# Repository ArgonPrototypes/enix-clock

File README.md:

# Enix: The Modern Nixie Clock
### A beautifully sleek product that gives new life to vintage components
#### Learn more at our website: https://www.argonprototypes.com/
This repository contains hardware, software, CAD files, and much more!

# More info about each section:
## Electronic Hardware:
The circuit board was designed in EAGLE CAD V9.2.2. Most dimensions are in mm on this board. The Gerber files are in RS-274X and Excellon drill format. There are several external libraries used; Sparkfun, Adafruit, MacroFab, and a couple more for unique parts. There should not be any problems with opening the design files without the libraries installed.

## Software:
The majority of the software is written in VS Code with the PlatformIO extension, however the Arduino IDE works just as well. The microcontroller used is the ATMega32u4, which has an 8 bit architecture with a 16MHz clock speed, is 5V tolerant, and includes built in USB programmability. This microcontroller is found on the Arduino Micro, which can be selected from the IDE to be able to upload to the board.<br/> The libraries used are Arduino.h, TimerOne.h, RTClib.h, Adafruit_NeoPixel.h, Adafruit MCP9808.h, Wire.h, and EEPROM.h.

## Case
The outer case is a CNC milled block of Aluminum or Wood. The Aluminum cases are Vapour Blasted to give a satin look, and then Anodized in Black or Clear to add a protective coating. The Wood cases are sanded to a smooth finish, prior to coating in polyurethane or oil. <br/> To hold the electronics in the case, there is a 3D printed bottom plate which uses heat set inserts to bolt to the circuit board.

## Packaging
To safely ship the Enix, a custom cardboard box with the internal dimensions of 6x6x3" was designed and ordered through Packlane. 2 Foam CNC milled inserts tightly pack the clock and all included accessories, which includes the Enix, some stickers, a drink coaster, instruction manual, and a Mini-USB cable.<br/>
The Packlane box is shipped in a larger 8x8x5" standard cardboard box filled with packing peanuts to give added protection in shipping.

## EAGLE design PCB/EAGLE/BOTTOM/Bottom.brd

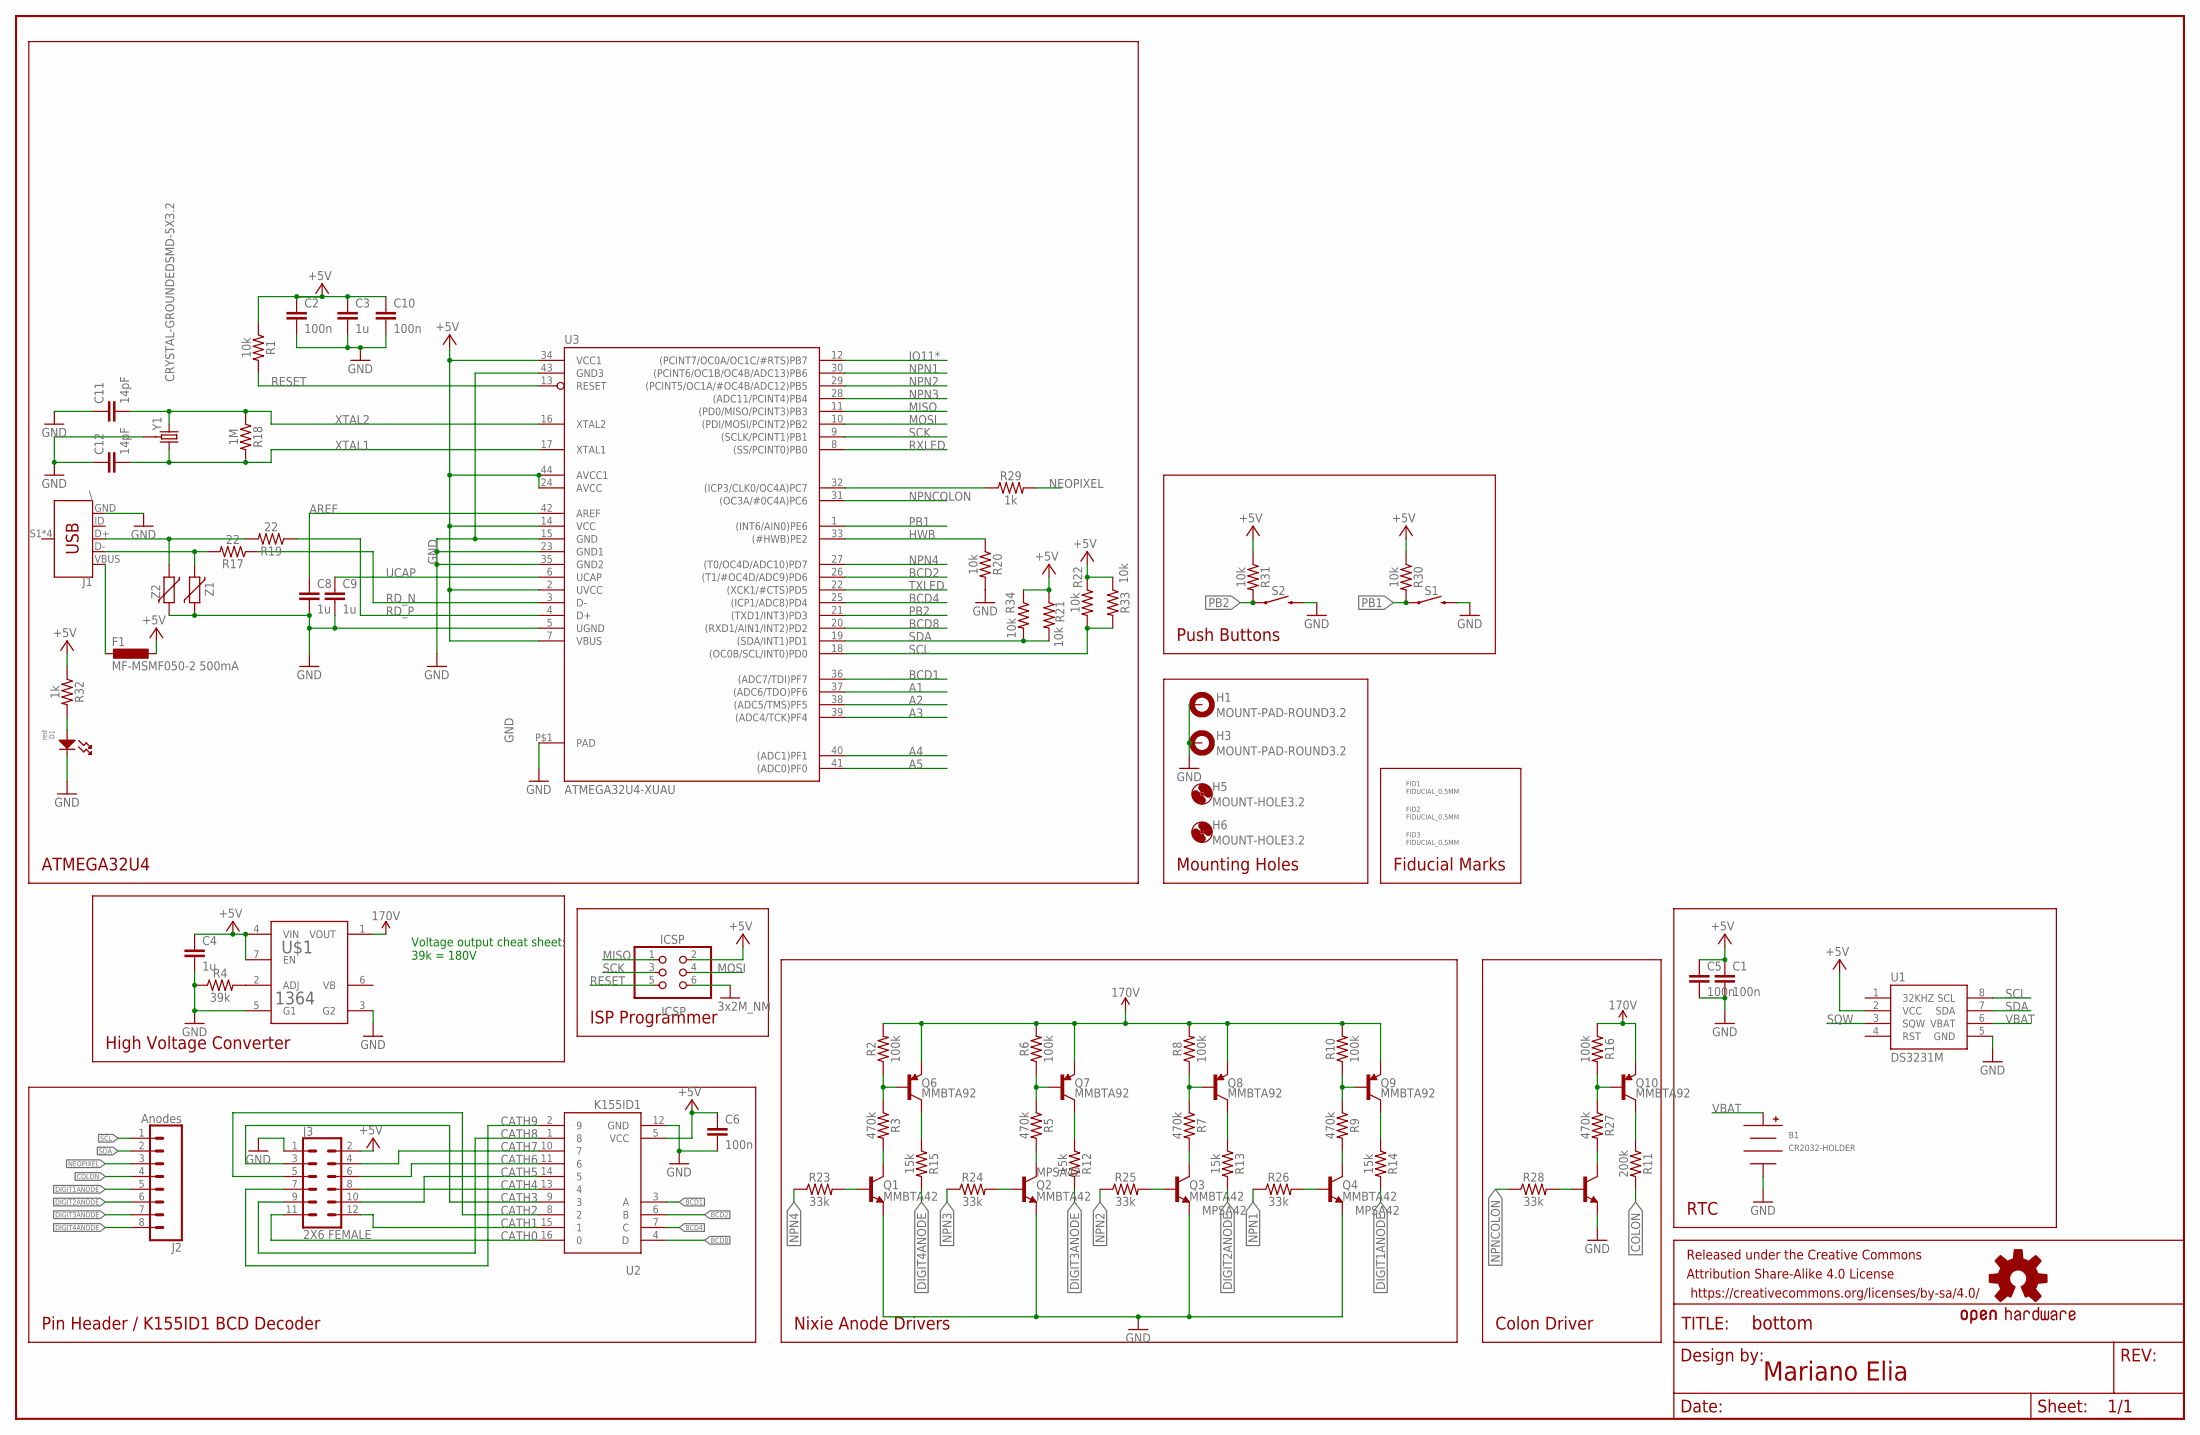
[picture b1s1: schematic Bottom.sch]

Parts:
B1: CR2032-HOLDER; CH28-2032LF
C1, C2, C5, C6, C10: 100n; 0805
C3, C4, C8, C9: 1u; 0805
C11, C12: 14pF; 0805
D1: red; LED0805
F1: MF-MSMF050-2 500mA; L1812
FID1, FID2, FID3: FIDUCIAL_0.5MM
FRAME1: FRAME-LEDGER; CREATIVE_COMMONS
H1, H3: MOUNT-PAD-ROUND3.2; 3,2-PAD
H5, H6: MOUNT-HOLE3.2; 3,2
ICSP: ICSP; 2X03
J1: \; USB-MINIB
J2: Anodes; 1X08_NO_SILK
J3: 2X6 FEMALE; 2X6_NOSILK
LOGO1: OSHW-LOGOL; OSHW-LOGO-L
Q1, Q2, Q3, Q4, Q5: MMBTA42; SOT23-3
Q6, Q7, Q8, Q9, Q10: MMBTA92; SOT23-3
R1, R20, R21, R22, R30, R31, R33, R34: 10k; 0805
R2, R6, R8, R10, R16: 100k; 0805
R3, R5, R7, R9, R27: 470k; 0805
R4: 39k; 0805
R11: 200k; 0805
R12, R13, R14, R15: 15k; 0805
R17, R19: 22; 0805
R18: 1M; 0805
R23, R24, R25, R26, R28: 33k; 0805
R29, R32: 1k; 0805
S1, S2: MOMENTARY-SWITCH-SPST-PTH-RIGHT-ANGLE-KIT; TACTILE_SWITCH_PTH_RIGHT_ANGLE_KIT
U1: DS3231M; SO08
U2: K155ID1; DIL16-KIT
U3: ATMEGA32U4-XUAU; TQFP44-PAD
U$1: 1364
Y1: CRYSTAL-GROUNDEDSMD-5X3.2; CRYSTAL-SMD-5X3.2-4PAD
Z1, Z2: VARISTORCN0603; CT/CN0603

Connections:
170V: Q6.2 (E), Q7.2 (E), Q8.2 (E), Q9.2 (E), Q10.2 (E), R2.2, R6.2, R8.2, R10.2, R16.1, U$1.1 (VOUT)
+5V: C1.1, C2.1, C3.1, C4.1, C5.1, C6.1, C10.1, F1.1, ICSP.2, J3.2, R1.1, R21.1, R22.1, R30.1, R31.1, R32.1, R33.1, R34.1, U1.2 (VCC), U2.5 (VCC), U3.2 (UVCC), U3.7 (VBUS), U3.14 (VCC), U3.24 (AVCC), U3.34 (VCC1), U3.44 (AVCC1), U$1.4 (VIN), U$1.7 (EN)
A1: U3.37 ((ADC6/TDO)PF6)
A2: U3.38 ((ADC5/TMS)PF5)
A3: U3.39 ((ADC4/TCK)PF4)
A4: U3.40 ((ADC1)PF1)
A5: U3.41 ((ADC0)PF0)
AREF: C8.1, U3.42 (AREF)
BCD1: U2.3 (A), U3.36 ((ADC7/TDI)PF7)
BCD2: U2.6 (B), U3.26 ((T1/#OC4D/ADC9)PD6)
BCD4: U2.7 (C), U3.25 ((ICP1/ADC8)PD4)
BCD8: U2.4 (D), U3.20 ((RXD1/AIN1/INT2)PD2)
CATH0: J3.11, U2.16 (0)
CATH1: J3.12, U2.15 (1)
CATH2: J3.5, U2.8 (2)
CATH3: J3.3, U2.9 (3)
CATH4: J3.8, U2.13 (4)
CATH5: J3.10, U2.14 (5)
CATH6: J3.6, U2.11 (6)
CATH7: J3.4, U2.10 (7)
CATH8: J3.9, U2.1 (8)
CATH9: J3.7, U2.2 (9)
COLON: J2.4, R11.2
DIGIT1ANODE: J2.5, R14.2
DIGIT2ANODE: J2.6, R13.2
DIGIT3ANODE: J2.7, R12.2
DIGIT4ANODE: J2.8, R15.2
D_N: J1.D-, R17.2, Z1.1
D_P: J1.D+, R19.2, Z2.1
GND: B1.NEG, C1.2, C2.2, C3.2, C4.2, C5.2, C6.2, C8.2, C9.2, C10.2, C11.1, C12.1, D1.CATHODE, H1.B3,2, H3.B3,2, ICSP.6, J1.GND, J3.1, Q1.2 (E), Q2.2 (E), Q3.2 (E), Q4.2 (E), Q5.2 (E), R4.1, R20.2, S1.2, S2.2, U1.5 (GND), U2.12 (GND), U3.5 (UGND), U3.15 (GND), U3.23 (GND1), U3.35 (GND2), U3.43 (GND3), U3.P$1 (PAD), U$1.3 (G2), U$1.5 (G1), Y1.2 (3), Y1.4 (3), Z1.2, Z2.2
HWB: R20.1, U3.33 ((#HWB)PE2)
IO11*: U3.12 ((PCINT7/OC0A/OC1C/#RTS)PB7)
MISO: ICSP.1, U3.11 ((PD0/MISO/PCINT3)PB3)
MOSI: ICSP.4, U3.10 ((PDI/MOSI/PCINT2)PB2)
unnamed: Q1.1 (B), R23.2
unnamed: Q2.1 (B), R24.2
unnamed: R4.2, U$1.2 (ADJ)
unnamed: Q3.1 (B), R25.2
unnamed: Q4.1 (B), R26.2
unnamed: Q6.1 (B), R2.1, R3.1
unnamed: Q1.3 (C), R3.2
unnamed: Q7.1 (B), R5.1, R6.1
unnamed: Q8.1 (B), R7.1, R8.1
unnamed: Q9.1 (B), R9.1, R10.1
unnamed: Q4.3 (C), R9.2
unnamed: Q2.3 (C), R5.2
unnamed: Q3.3 (C), R7.2
unnamed: Q5.1 (B), R28.2
unnamed: Q10.1 (B), R16.2, R27.1
unnamed: R29.1, U3.32 ((ICP3/CLK0/OC4A)PC7)
unnamed: Q5.3 (C), R27.2
unnamed: D1.ANODE, R32.2
unnamed: Q10.3 (C), R11.1
unnamed: Q7.3 (C), R12.1
unnamed: Q6.3 (C), R15.1
unnamed: Q8.3 (C), R13.1
unnamed: Q9.3 (C), R14.1
NEOPIXEL: J2.3, R29.2
NPN1: R26.1, U3.30 ((PCINT6/OC1B/OC4B/ADC13)PB6)
NPN2: R25.1, U3.29 ((PCINT5/OC1A/#OC4B/ADC12)PB5)
NPN3: R24.1, U3.28 ((ADC11/PCINT4)PB4)
NPN4: R23.1, U3.27 ((T0/OC4D/ADC10)PD7)
NPNCOLON: R28.1, U3.31 ((OC3A/#0C4A)PC6)
PB1: R30.2, S1.1, U3.1 ((INT6/AIN0)PE6)
PB2: R31.2, S2.1, U3.21 ((TXD1/INT3)PD3)
RD_N: R17.1, U3.3 (D-)
RD_P: R19.1, U3.4 (D+)
RESET: ICSP.5, R1.2, U3.13 (RESET)
RXLED: U3.8 ((SS/PCINT0)PB0)
SCK: ICSP.3, U3.9 ((SCLK/PCINT1)PB1)
SCL: J2.1, R22.2, R33.2, U1.8 (SCL), U3.18 ((OC0B/SCL/INT0)PD0)
SDA: J2.2, R21.2, R34.2, U1.7 (SDA), U3.19 ((SDA/INT1)PD1)
SQW: U1.3 (SQW)
TXLED: U3.22 ((XCK1/#CTS)PD5)
UCAP: C9.1, U3.6 (UCAP)
VBAT: B1.POS, U1.6 (VBAT)
VBUS: F1.2, J1.VBUS
XTAL1: C12.2, R18.2, U3.17 (XTAL1), Y1.1 (2)
XTAL2: C11.2, R18.1, U3.16 (XTAL2), Y1.3 (1)

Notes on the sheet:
ATMEGA32U4
High Voltage Converter
Pin Header / K155ID1 BCD Decoder
Nixie Anode Drivers
Colon Driver
RTC
Mariano Elia
Push Buttons
Mounting Holes
Fiducial Marks
ISP Programmer
Voltage output cheat sheet: 39k = 180V

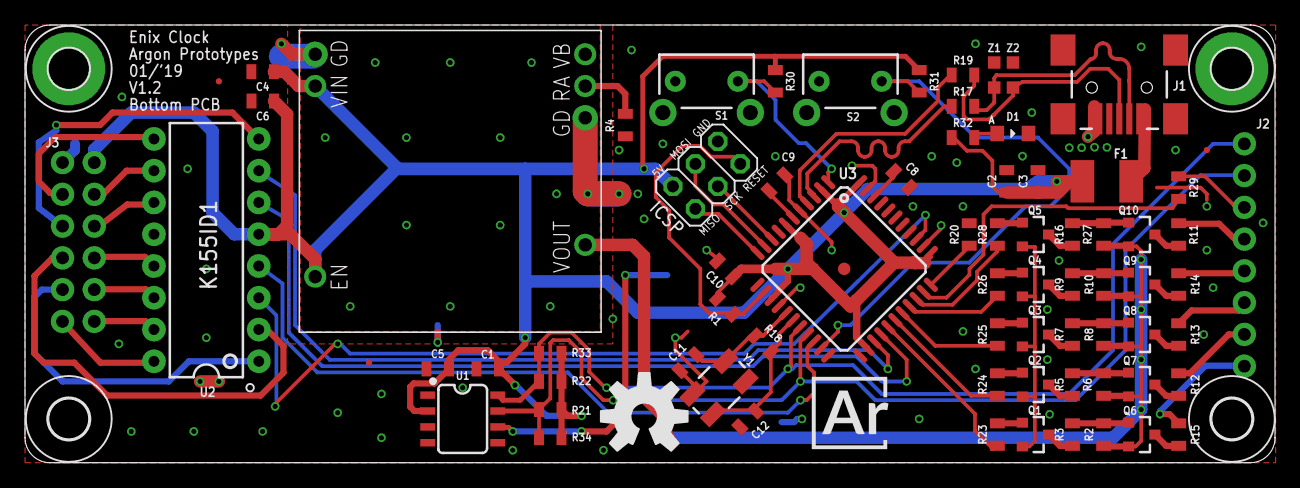
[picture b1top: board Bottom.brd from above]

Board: 2 copper layers, 100.0 x 35.0 mm, 80 parts (1 on the bottom side), 70 nets.

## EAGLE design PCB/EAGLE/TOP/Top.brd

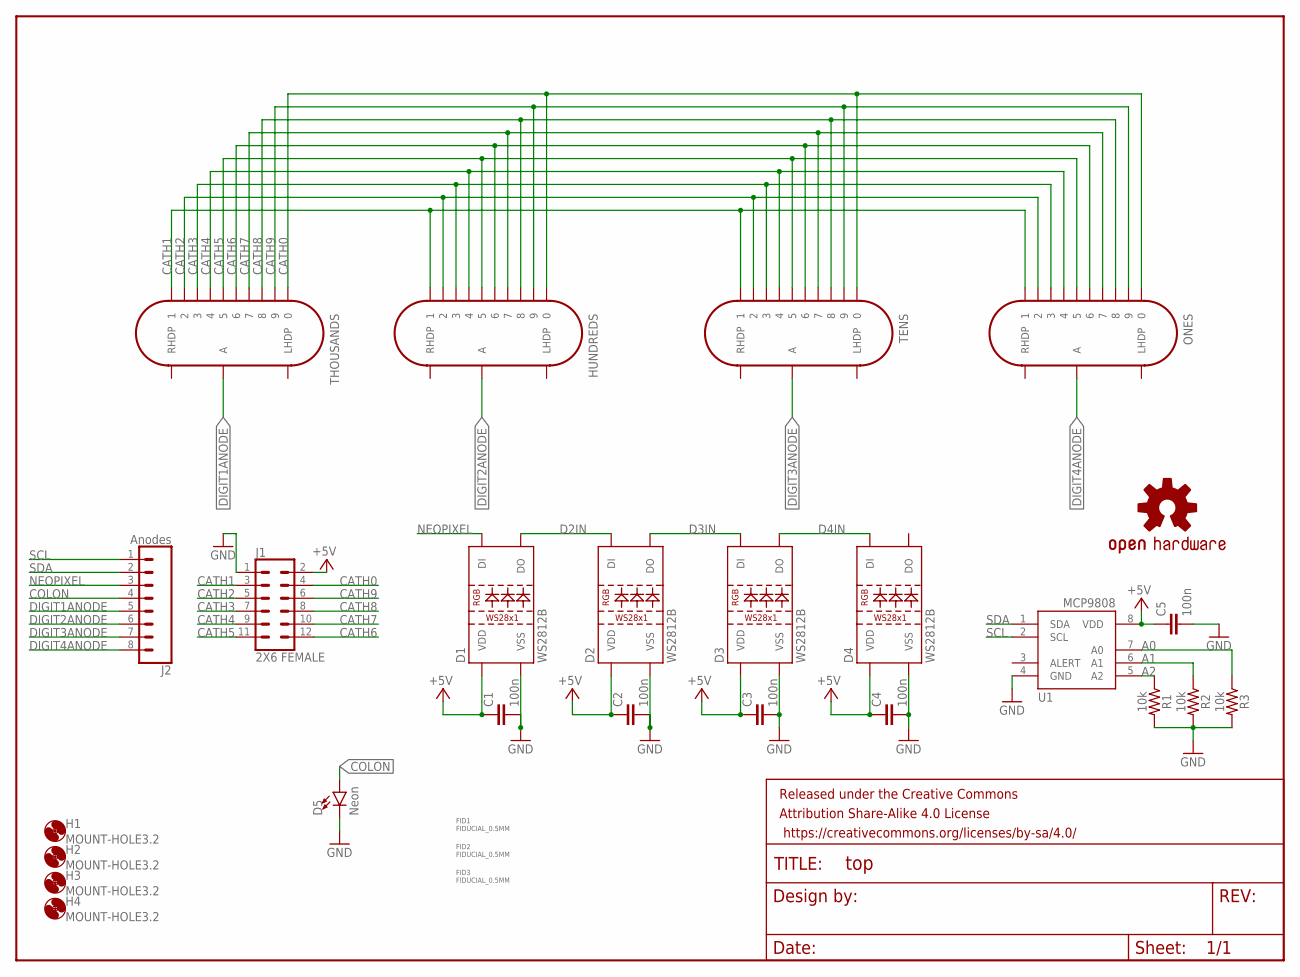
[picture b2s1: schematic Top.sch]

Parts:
C1, C2, C3, C4, C5: 100n; 0805
D1, D2, D3, D4: WS2812B
D5: Neon; LED_5MM
FID1, FID2, FID3: FIDUCIAL_0.5MM
FRAME1: FRAME-LETTER; CREATIVE_COMMONS
H1, H2, H3, H4: MOUNT-HOLE3.2; 3,2
HUNDREDS: IN-14
J1: 2X6 FEMALE; 2X6_NOSILK
J2: Anodes; 1X08_NO_SILK
LOGO1: OSHW-LOGOM; OSHW-LOGO-M
ONES: IN-14
R1, R2, R3: 10k; 0805
TENS: IN-14
THOUSANDS: IN-14
U1: MCP9808-E/MS; MSOP8_0.65MM

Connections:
+5V: C1.1, C2.1, C3.1, C4.1, C5.1, D1.1 (VDD), D2.1 (VDD), D3.1 (VDD), D4.1 (VDD), J1.2, U1.8 (VDD)
A0: R3.1, U1.7 (A0)
A1: R2.1, U1.6 (A1)
A2: R1.1, U1.5 (A2)
CATH0: HUNDREDS.1 (0), J1.4, ONES.1 (0), TENS.1 (0), THOUSANDS.1 (0)
CATH1: HUNDREDS.0 (1), J1.3, ONES.0 (1), TENS.0 (1), THOUSANDS.0 (1)
CATH2: HUNDREDS.9 (2), J1.5, ONES.9 (2), TENS.9 (2), THOUSANDS.9 (2)
CATH3: HUNDREDS.8 (3), J1.7, ONES.8 (3), TENS.8 (3), THOUSANDS.8 (3)
CATH4: HUNDREDS.7 (4), J1.9, ONES.7 (4), TENS.7 (4), THOUSANDS.7 (4)
CATH5: HUNDREDS.6 (5), J1.11, ONES.6 (5), TENS.6 (5), THOUSANDS.6 (5)
CATH6: HUNDREDS.5 (6), J1.12, ONES.5 (6), TENS.5 (6), THOUSANDS.5 (6)
CATH7: HUNDREDS.4 (7), J1.10, ONES.4 (7), TENS.4 (7), THOUSANDS.4 (7)
CATH8: HUNDREDS.3 (8), J1.8, ONES.3 (8), TENS.3 (8), THOUSANDS.3 (8)
CATH9: HUNDREDS.2 (9), J1.6, ONES.2 (9), TENS.2 (9), THOUSANDS.2 (9)
COLON: D5.A, J2.4
D2IN: D1.2 (DO), D2.4 (DI)
D3IN: D2.2 (DO), D3.4 (DI)
D4IN: D3.2 (DO), D4.4 (DI)
DIGIT1ANODE: J2.5, THOUSANDS.A
DIGIT2ANODE: HUNDREDS.A, J2.6
DIGIT3ANODE: J2.7, TENS.A
DIGIT4ANODE: J2.8, ONES.A
GND: C1.2, C2.2, C3.2, C4.2, C5.2, D1.3 (VSS), D2.3 (VSS), D3.3 (VSS), D4.3 (VSS), D5.K (C), J1.1, R1.2, R2.2, R3.2, U1.4 (GND)
NEOPIXEL: D1.4 (DI), J2.3
SCL: J2.1, U1.2 (SCL)
SDA: J2.2, U1.1 (SDA)

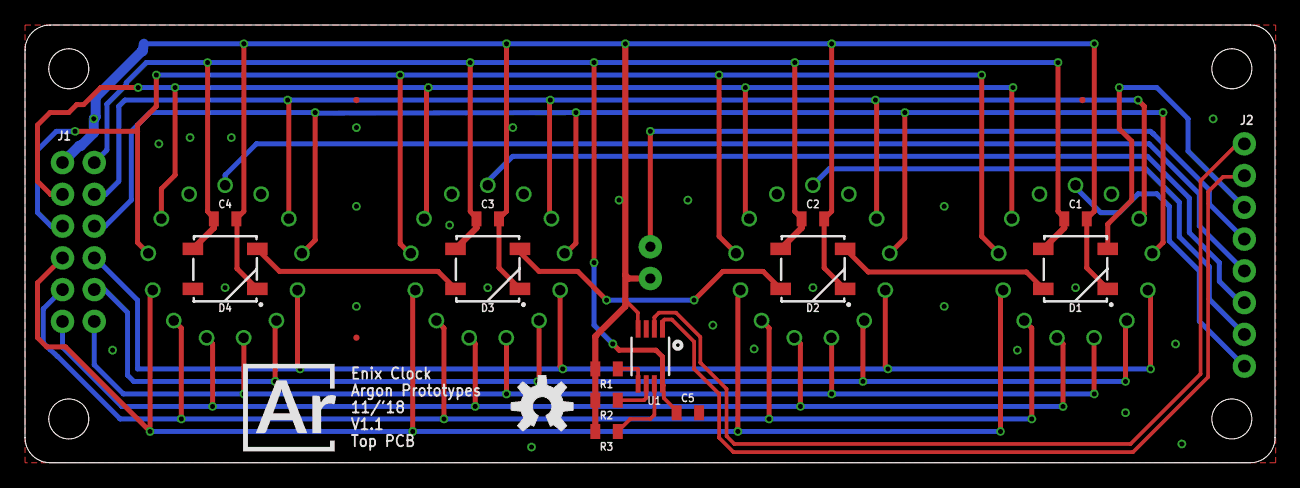
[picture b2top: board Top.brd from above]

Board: 2 copper layers, 100.0 x 35.0 mm, 29 parts (0 on the bottom side), 26 nets.

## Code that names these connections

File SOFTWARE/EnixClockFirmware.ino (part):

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/*
  Format: (Hardware Pin Name - Software Name)

  //PORTB = 0b(PB7)(PB6-ANODE1)(PB5-ANODE2)(PB4-ANODE3)(PB3)(PB2)(PB1)(PB0)
  //PORTC = 0b(PC7-NEOPIXEL)(PC6-COLON)(NOT USED)(NOT USED)(NOT USED)(NOT USED)(NOT USED)(NOT USED)
  //PORTD = 0b(PD7-ANODE4)(PD6-BCD2)(PD5)(PD4-BCD4)(PD3-PUSHBUTTON2)(PD2-BCD8)(PD1)(PD0)
  //PORTE = 0b(NOT USED)(PE6-PUSHBUTTON1)(NOT USED)(NOT USED)(NOT USED)(PE2)(NOT USED)(NOT USED)
  //PORTF = 0b(PF7-BCD1)(PF6)(PF5)(PF4)(NOT USED)(NOT USED)(PF1)(PF0)
*/

#define ANODE1 10 // PB6
#define ANODE2 9  // PB5
#define ANODE3 8  // PB4
#define ANODE4 6  // PD7

#define BCD1 A0 // PF7
#define BCD2 12 // PD6
#define BCD4 4  // PD4
#define BCD8 0  // PD2

#define NEOPIXEL 13 // PC7
#define COLON 5     // PC6

// 2 Push Buttons
#define PUSHBUTTON1 7 // PE6 "Menu button"
#define PUSHBUTTON2 1 // PD3 "Increment button"

// EEPROM addresses
const uint8_t BITCHECK_ADDRESS = 0; //One-time run code
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  //A set bit (1) in a register indicates that the pin is an output.
  //Clearing a bit (0) sets the pin as an input
  DDRB |= 0b01110000; //Set outputs ANODE1, ANODE2, ANODE3 //pinMode(ANODE1, OUTPUT); pinMode(ANODE2, OUTPUT); pinMode(ANODE3, OUTPUT);
  DDRC |= 0b11000000; //Set outputs NEOPIXEL, COLON // pinMode(COLON, OUTPUT);
  DDRD |= 0b11010100; //Set outputs ANODE4, BCD2, BCD4, BCD8 // pinMode(ANODE4, OUTPUT);  pinMode(BCD2, OUTPUT); pinMode(BCD4, OUTPUT); pinMode(BCD8, OUTPUT);
  DDRD &= 0b11110111; //Clear input PUSHBUTTON2 // pinMode(PUSHBUTTON2, INPUT);
  DDRE &= 0b10111111; //Clear input PUSHBUTTON1 // pinMode(PUSHBUTTON1, INPUT);
  DDRF |= 0b10000000; //Set output BCD1 // pinMode(BCD1, OUTPUT);
}

void setupTimer()
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   8. Under lighting  : All 4 L.E.D's light up to signify the chosen color. Order is none, rainbow, then several static colors.
   9. Under lighting brightness : 1 to 5. Displayed on the right 2 digits, with all under lighting on in the selected color, otherwise in pink to show brightness. 
   10. Temperature Units : Celsius or Fahrenheit. Displays the current temperature in either unit on the right 2 digits, with red under lighting.
   11. Temperature Offset : -7 to 7 in degrees Celsius (Each degree C is 1.8 degrees F). Displayed on the right 2 digits with pink under lighting. The center neon colon acts as a negative sign.
   12. Mode Select    : 1 to 4. Shown on the right 2 digits with blue underlighting.
                          Mode 1: Time, Date, Temperature
                          Mode 2: Time, Date
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void clearAnodes()
{
  //Clear Anodes
  PORTB &= 0b10001111; //Clear Anode (1,2,3) aka (PB6,PB5,PB4) aka (D10, D9, D8)
  PORTD &= 0b01111111; //Clear Anode (4) aka (PD7) aka D6
}

uint8_t setAnodeForCurDigit()
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  {
    switch (currentDigit)
    {
    case 0: //Set PB6
      if (shouldAnodeBeOn(enableDigits, 3))
      { //check if anode should be turned on
        currentNumber = (int)(currentBuffer / 100 / 10) % 10;
        PORTB |= 0b01000000; // Set Anode 1 PB6
      }
      break;

    case 1: //Set PB5
      if (shouldAnodeBeOn(enableDigits, 2))
      {
        PORTB |= 0b00100000;
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  uint8_t currentNumber;
  switch (currentDigit)
  {
  case 0: //Set PB6
    PORTB |= 0b00010000;
    currentNumber = (currentBuffer / 10) % 10;
    break;

  case 1: //Set PB5

    PORTD |= 0b10000000;
    currentNumber = currentBuffer % 10;
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  uint8_t currentNumber;
  switch (currentDigit)
  {
  case 0: //Set PB6
    PORTB |= 0b00100000;
    currentNumber = (currentBuffer / 100) % 10;
    break;

  case 1: //Set PB5
    PORTB |= 0b00100000;
    currentNumber = (currentBuffer / 100) % 10;
    break;
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  uint8_t currentNumber;
  switch (currentDigit)
  {
  case 0: //Set PB6
    currentNumber = (int)(currentBuffer / 100 / 10) % 10;
    PORTB |= 0b01000000; // Set Anode 1 PB6
    break;

  case 1:
    currentNumber = (currentBuffer / 100) % 10;
    PORTB |= 0b00100000; // Set Anode 2 PB5
    break;

  case 2:
    currentNumber = (int)(currentBuffer / 100 / 10) % 10;
    PORTB |= 0b01000000; // Set Anode 1 PB6
    break;

  case 3:
    currentNumber = (currentBuffer / 100) % 10;
    PORTB |= 0b00100000; // Set Anode 2 PB5
    break;
  }
  return currentNumber;
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void clearBCD()
{
  //Clear BCD
  PORTD &= 0b10101011; //Clear BCD (2,4,8) aka (PD6,PD4,PD2) aka (D12,D4,D0)
  PORTF &= 0b01111111; //Clear BCD (1) aka (PF7) aka (A0)
}

void setBCD(uint8_t currentNumber)
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  //Switch case from 0-9
  switch (currentNumber)
  {
  //As reference BCD: 1248, PF7,PD6,PD4,PD2
  case 0: //BCD: 1110: Set PF7, PD6, and PD4
    PORTF |= 0b10000000;
    PORTD |= 0b01010000;
    break;

  case 1: //BCD: 1100: Set PF7 and PD6
    PORTF |= 0b10000000;
    PORTD |= 0b01000000;
    break;

  case 2: //BCD: 0100: Set PD6
    PORTD |= 0b01000000;
    break;

  case 3: //BCD: 1001: Set PF7 and PD2
    PORTF |= 0b10000000;
    PORTD |= 0b00000100;
    break;

  case 4: //BCD: 0001: Set PD2
    PORTD |= 0b00000100;
    break;

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    //Leave outputs as 0's
    break;

  case 6: //BCD: 1000: Set PF7
    PORTF |= 0b10000000;
    break;

  case 7: //BCD: 1010: Set PF7 and PD4
    PORTF |= 0b10000000;
    PORTD |= 0b00010000;
    break;

  case 8: //BCD: 0010: Set PD4
    PORTD |= 0b00010000;
    break;

  case 9: //BCD: 0110: Set PD6 and PD4
    PORTD |= 0b01010000;
    break;
  }
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
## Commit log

2018-09-12 Add README
2018-09-12 Add GitHub issue and PR templates
2018-09-13 Add sub folder for github issue reporting. Bug report, feature request, and questions
2018-09-13 Add .gitignore for .DS_Store
2018-11-14 Add gerber files, and eagle files
2018-11-14 Separate Gerber and Eagle into 2 separate folders
2018-11-14 Add datasheets
2018-11-14 Add Pictures folder
2018-11-14 remove sub folder
2018-11-15 Add images of circuitboards
2020-03-02 Add files
2020-03-02 Readme Update
2020-03-03 Add Logo and Artwork
2020-03-03 Update README for packaging, jigs, and case
2020-05-11 Update boards to latest, update packaging photos, add 3D printed part files
2020-07-14 Publish software file and update README
2020-07-15 Move Arduino software in folder to make the IDE happy
2020-07-16 Make duration configurable per mode

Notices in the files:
parts and their libraries:
SparkFun-Connectors: Licensing: Creative Commons ShareAlike 4.0 International - https://creativecommons.org/licenses/by-sa/4.0
SparkFun-Aesthetics: Released under the Creative Commons Attribution Share-Alike 4.0 License
SparkFun-Aesthetics: https://creativecommons.org/licenses/by-sa/4.0
